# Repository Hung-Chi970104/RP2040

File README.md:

# RP2040 Hacker Board
- Demo video (with radio nrf24l01): https://youtu.be/eCMlnlmFBuc
- Demo video (radio control nrf24l01): https://youtu.be/_LA9TkBpY54

- Upgraded flash storage from 2MB (W25Q16JVUXIQ TR) to 16MB (W25Q64JVXGIQ)
- Replaced MCP1700x-330xxTT (linear regulator) with RT6154AGQW (buck-boost switching regulator)
- Added Schottky Diode to allow external power supply
- Added a RESET button
- Changed 33pF crystal cap to 15pF to match the crystal I ordered

## Components
- RP2040
- 12MHz Crystal (ABM8-272-T3)
- 8MB Flash Storage (W25Q64JVXGIQ)
- Buck-Boost Switching Regulator (RT6154AGQW)
- USB-C (TYPE-C-31-M-12)

## Pinouts
| Pin Number (Left) | Description | Pin Number (Right) | Description |
| ------------- | ------------- | ------------- | ------------- |
| 1 | GPIO0 | 1 | VBUS |
| 2 | GPIO1 | 2 | VSYS |
| 3 | GND | 3 | GND |
| 4 | GPIO2 | 4 | GPIO28_ADC2 |
| 5 | GPIO3 | 5 | GPIO27_ADC1 |
| 6 | GPIO4 | 6 | 3V3 |
| 7 | GPIO5 | 7 | GPIO26_ADC0 |
| 8 | BOOTSEL | 8 | GND |
| 9 | GPIO6 | 9 | GPIO25 |
| 10 | GPIO7 | 10 | GPIO24 |
| 11 | GPIO8 | 11 | GPIO23 |
| 12 | GPIO9 | 12 | GPIO22 |
| 13 | GND | 13 | GND |
| 14 | GPIO10 | 14 | GPIO21 |
| 15 | GPIO11 | 15 | GPIO20 |
| 16 | GPIO12 | 16 | GPIO19 |
| 17 | GPIO13 | 17 | GND |
| 18 | GND | 18 | GPIO18 |
| 19 | GPIO14 | 19 | GPIO17 |
| 20 | GPIO15 | 20 | GPIO16 |

## PCBs

- 2 layers
- Single-sided component placement
- 2.6mm board thickness
- HASL (with lead) surface finish
- 1oz outer copper weight

### PCB Schematic

### PCB Layouts

### 3D Model

## Rendered Demo

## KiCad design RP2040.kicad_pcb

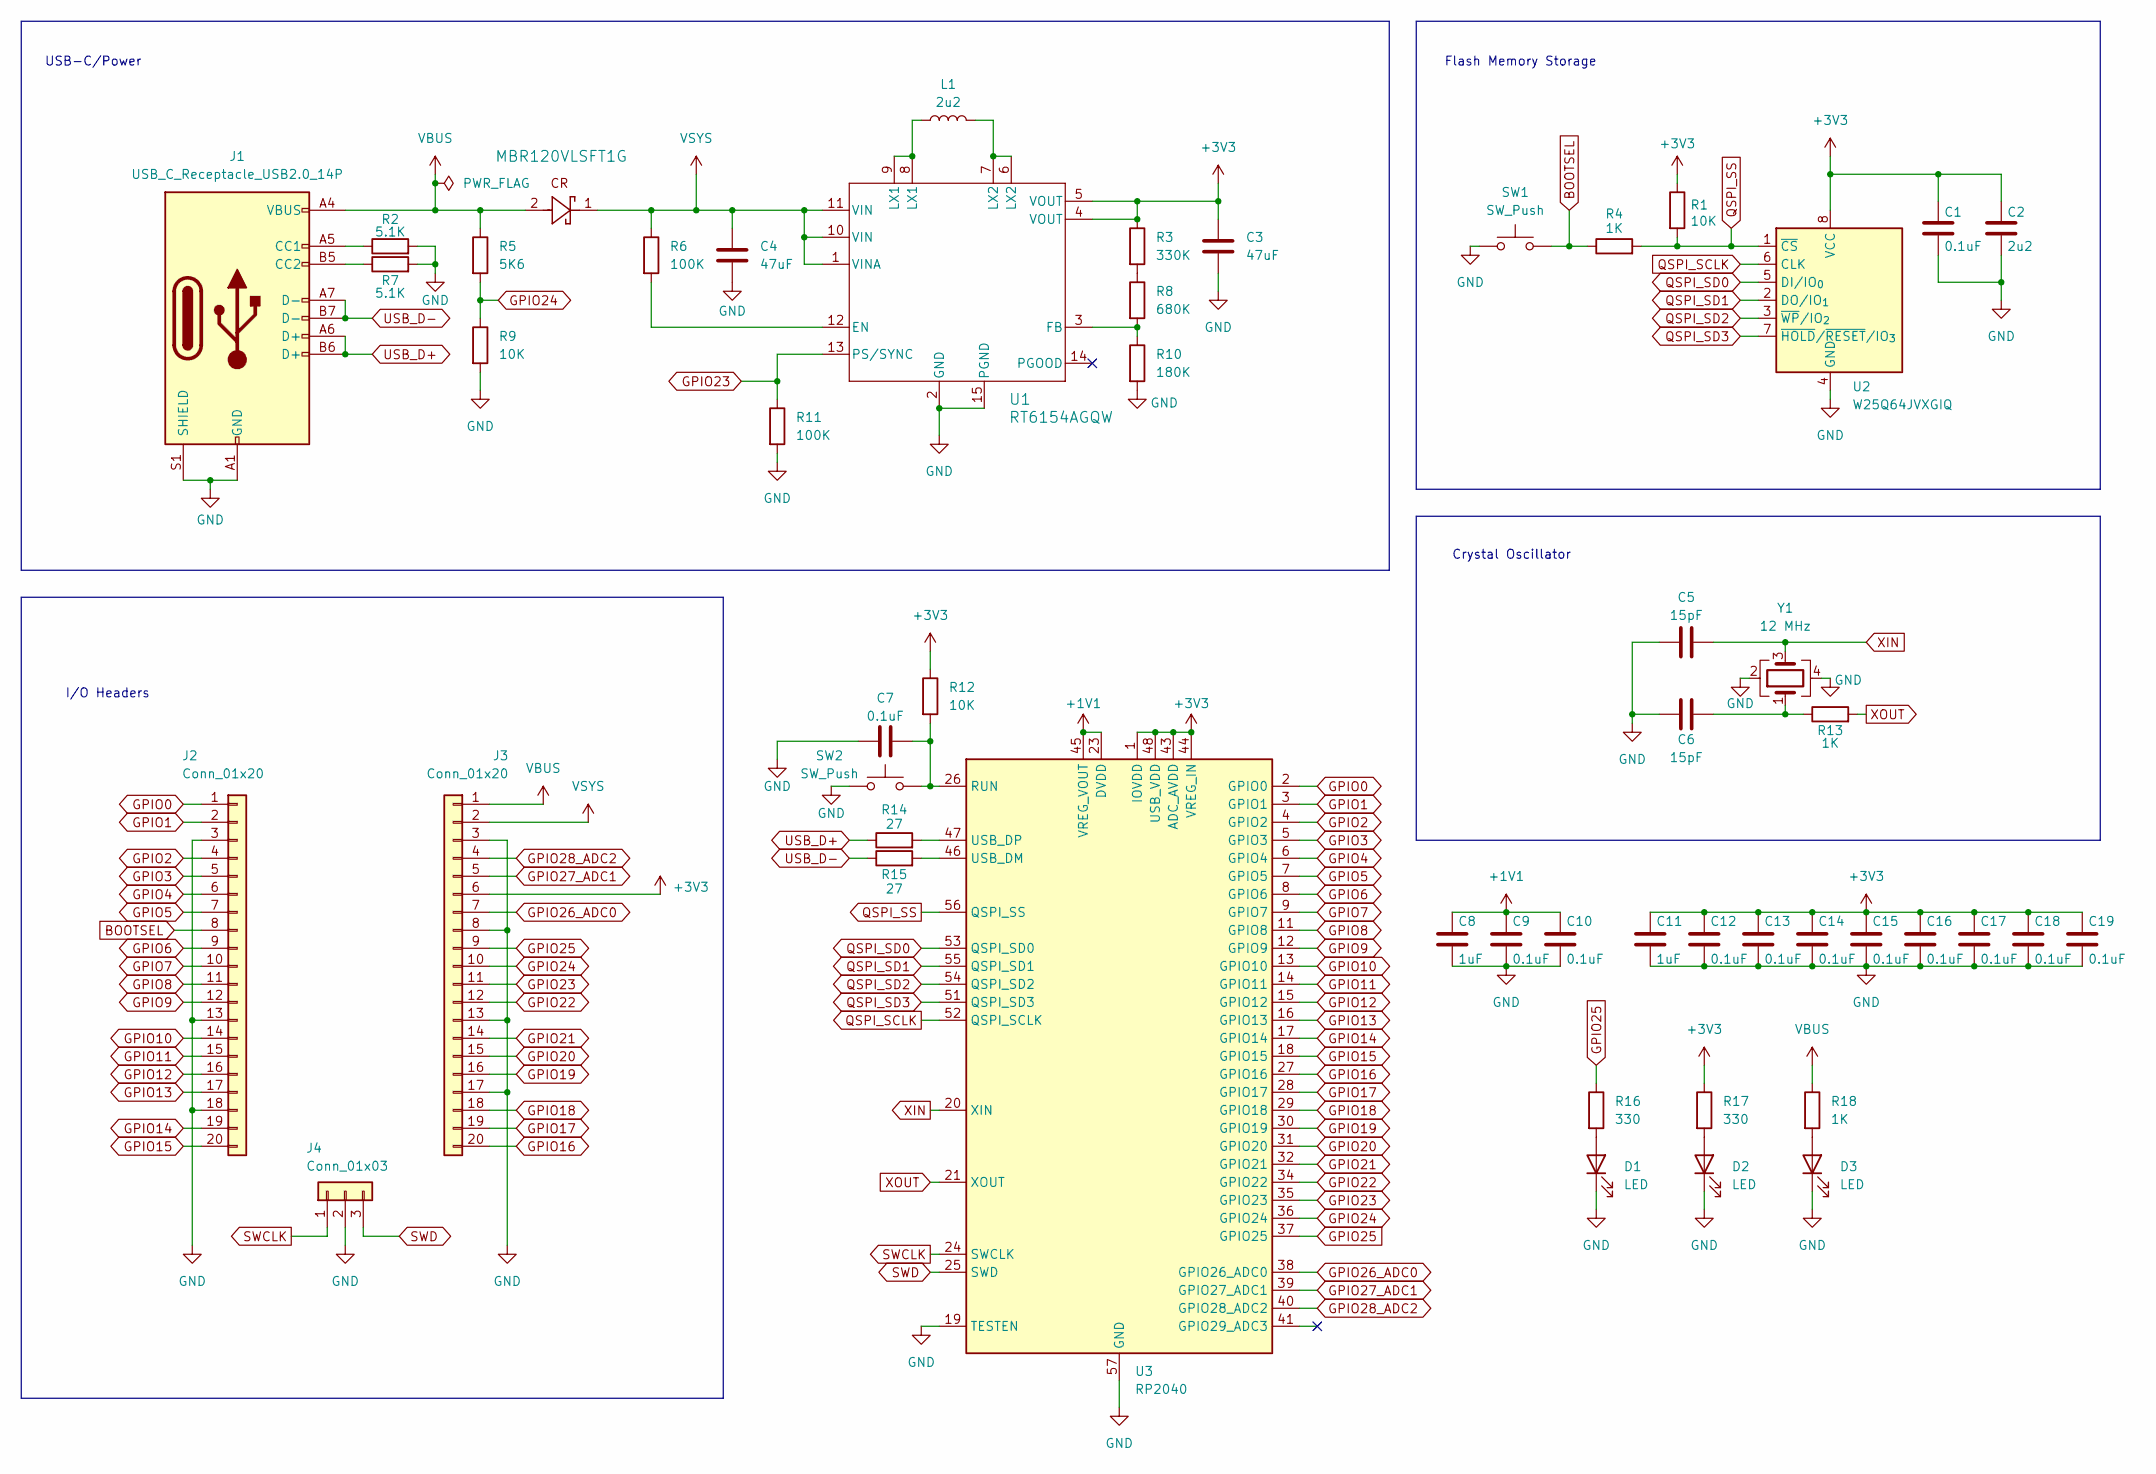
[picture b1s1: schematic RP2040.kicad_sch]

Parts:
111111111: MBR120VLSFT1G; SDO_SOD-123FL_ONS
C1, C7, C9, C10, C12, C13, C14, C15, C16, C17, C18, C19: 0.1uF; C_0402_1005Metric
C2: 2u2; C_0603_1608Metric
C3, C4: 47uF; C_0805_2012Metric
C5, C6: 15pF; C_0402_1005Metric
C8, C11: 1uF; C_0402_1005Metric
D1, D2, D3: LED; LED_0402_1005Metric
J1: USB_C_Receptacle_USB2.0_14P; USB_C_Receptacle_HRO_TYPE-C-31-M-12
J2, J3: Conn_01x20; PinHeader_1x20_P2.54mm_Vertical
J4: Conn_01x03; PinHeader_1x03_P2.54mm_Vertical
L1: 2u2; L_1008_2520Metric
R1, R9, R12: 10K; R_0402_1005Metric
R2, R7: 5.1K; R_0402_1005Metric
R3: 330K; R_0402_1005Metric
R4, R13, R18: 1K; R_0402_1005Metric
R5: 5K6; R_0402_1005Metric
R6, R11: 100K; R_0402_1005Metric
R8: 680K; R_0402_1005Metric
R10: 180K; R_0402_1005Metric
R14, R15: 27; R_0402_1005Metric
R16, R17: 330; R_0402_1005Metric
SW1, SW2: SW_Push; SW_Push_SPST_NO_Alps_SKRK
U1: RT6154AGQW; VSON-14_L4.0-W3.0-P0.50-BL-EP_TI_DSJ
U2: W25Q64JVXGIQ; XSON-8_L4.0-W4.0-P0.80-TL-EP
U3: RP2040; QFN-56-1EP_7x7mm_P0.4mm_EP3.2x3.2mm
Y1: 12 MHz; Crystal_SMD_3225-4Pin_3.2x2.5mm

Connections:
+1V1: C8.1, C9.1, C10.1, U3.23 (DVDD), U3.45 (VREG_VOUT), U3.50 (DVDD)
+3V3: C1.1, C2.1, C3.1, C11.1, C12.1, C13.1, C14.1, C15.1, C16.1, C17.1, C18.1, C19.1, J3.6, R1.1, R3.1, R12.1, R17.1, U1.4 (VOUT), U1.5 (VOUT), U2.8 (VCC), U3.1 (IOVDD), U3.10 (IOVDD), U3.22 (IOVDD), U3.33 (IOVDD), U3.42 (IOVDD), U3.43 (ADC_AVDD), U3.44 (VREG_IN), U3.48 (USB_VDD), U3.49 (IOVDD)
BOOTSEL: J2.8, R4.1, SW1.2
GND: C1.2, C2.2, C3.2, C4.2, C5.1, C6.1, C7.1, C8.2, C9.2, C10.2, C11.2, C12.2, C13.2, C14.2, C15.2, C16.2, C17.2, C18.2, C19.2, D1.1 (K), D2.1 (K), D3.1 (K), J1.A1 (GND), J1.A12 (GND), J1.B1 (GND), J1.B12 (GND), J1.S1 (SHIELD), J2.3, J2.13, J2.18, J3.3, J3.8, J3.13, J3.17, J4.2, R2.2, R7.2, R9.2, R10.2, R11.2, SW1.1, SW2.1, U1.2 (GND), U1.15 (PGND), U2.4 (GND), U3.19 (TESTEN), U3.57 (GND), Y1.2, Y1.4
GPIO0: J2.1, U3.2 (GPIO0)
GPIO1: J2.2, U3.3 (GPIO1)
GPIO2: J2.4, U3.4 (GPIO2)
GPIO3: J2.5, U3.5 (GPIO3)
GPIO4: J2.6, U3.6 (GPIO4)
GPIO5: J2.7, U3.7 (GPIO5)
GPIO6: J2.9, U3.8 (GPIO6)
GPIO7: J2.10, U3.9 (GPIO7)
GPIO8: J2.11, U3.11 (GPIO8)
GPIO9: J2.12, U3.12 (GPIO9)
GPIO10: J2.14, U3.13 (GPIO10)
GPIO11: J2.15, U3.14 (GPIO11)
GPIO12: J2.16, U3.15 (GPIO12)
GPIO13: J2.17, U3.16 (GPIO13)
GPIO14: J2.19, U3.17 (GPIO14)
GPIO15: J2.20, U3.18 (GPIO15)
GPIO16: J3.20, U3.27 (GPIO16)
GPIO17: J3.19, U3.28 (GPIO17)
GPIO18: J3.18, U3.29 (GPIO18)
GPIO19: J3.16, U3.30 (GPIO19)
GPIO20: J3.15, U3.31 (GPIO20)
GPIO21: J3.14, U3.32 (GPIO21)
GPIO22: J3.12, U3.34 (GPIO22)
GPIO23: J3.11, R11.1, U1.13 (PS/SYNC), U3.35 (GPIO23)
GPIO24: J3.10, R5.2, R9.1, U3.36 (GPIO24)
GPIO25: J3.9, R16.1, U3.37 (GPIO25)
GPIO26_ADC0: J3.7, U3.38 (GPIO26_ADC0)
GPIO27_ADC1: J3.5, U3.39 (GPIO27_ADC1)
GPIO28_ADC2: J3.4, U3.40 (GPIO28_ADC2)
unnamed: C6.2, R13.1, Y1.1
unnamed: D1.2 (A), R16.2
unnamed: D2.2 (A), R17.2
unnamed: D3.2 (A), R18.2
unnamed: J1.A5 (CC1), R2.1
unnamed: J1.B5 (CC2), R7.1
unnamed: L1.1, U1.8 (LX1), U1.9 (LX1)
unnamed: L1.2, U1.6 (LX2), U1.7 (LX2)
unnamed: R3.2, R8.1
unnamed: R6.2, U1.12 (EN)
unnamed: R8.2, R10.1, U1.3 (FB)
unnamed: C7.2, R12.2, SW2.2, U3.26 (RUN)
unnamed: R15.2, U3.46 (USB_DM)
unnamed: R14.2, U3.47 (USB_DP)
QSPI_SCLK: U2.6 (CLK), U3.52 (QSPI_SCLK)
QSPI_SD0: U2.5 (DI/IO_{0}), U3.53 (QSPI_SD0)
QSPI_SD1: U2.2 (DO/IO_{1}), U3.55 (QSPI_SD1)
QSPI_SD2: U2.3 (~WP/IO_{2}), U3.54 (QSPI_SD2)
QSPI_SD3: U2.7 (~HOLD/~RESET/IO_{3}), U3.51 (QSPI_SD3)
QSPI_SS: R1.2, R4.2, U2.1 (~CS), U3.56 (QSPI_SS)
SWCLK: J4.1, U3.24 (SWCLK)
SWD: J4.3, U3.25 (SWD)
USB_D+: J1.A6 (D+), J1.B6 (D+), R14.1
USB_D-: J1.A7 (D-), J1.B7 (D-), R15.1
VBUS: 111111111.2, J1.A4 (VBUS), J1.A9 (VBUS), J1.B4 (VBUS), J1.B9 (VBUS), J3.1, R5.1, R18.1
VSYS: 111111111.1, C4.1, J3.2, R6.1, U1.1 (VINA), U1.10 (VIN), U1.11 (VIN)
XIN: C5.2, U3.20 (XIN), Y1.3
XOUT: R13.2, U3.21 (XOUT)

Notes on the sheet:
Crystal Oscillator
I/O Headers
Flash Memory Storage
USB-C/Power

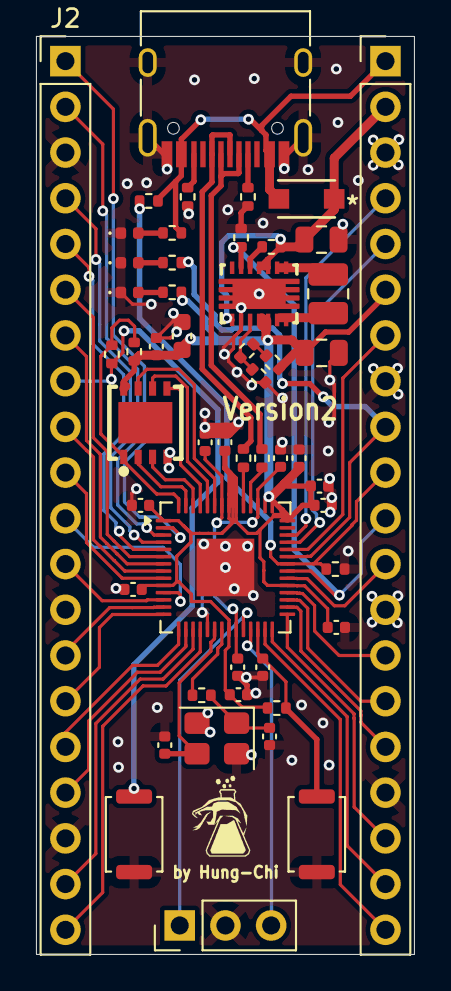
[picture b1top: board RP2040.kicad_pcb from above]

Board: 2 copper layers, 21.0 x 51.0 mm, 51 parts (0 on the bottom side), 61 nets.

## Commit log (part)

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2025-12-23 Add gitignore
2025-12-23 Completed PCB Design
2025-12-23 Added 3D models
2025-12-23 Fix grammar issues in README conclusion
    Corrected grammatical errors in the conclusion section.
2025-12-23 Update README with images and project conclusion
    Added images and expanded conclusion about the project experience.
2025-12-23 Fix image links and typos in README
    Updated image links in the README and corrected typos.
2025-12-24 Refactor README structure and add replication instructions
    Updated README to improve structure and clarity by adding sections for 'How to replicate' and correcting headings.
2025-12-27 Update Schematic and PCB
2026-01-09 Cleaned up silkscreen labeles
2026-02-23 Update Readme + Images
2026-02-27 update image
